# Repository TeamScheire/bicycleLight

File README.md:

# Team Scheire BicycleLight voor Carmen

Deze repository bevat de code en hardware schemas van twee deelprojecten:

1. CME (Het fietslicht en alle aanpassingen voor Carmen haar fiets)
2. SmartLight (het slimme fietslicht waarmee je een positive of negatieve fietservaring kan meedelen)

## 1. CME

In [deze folder](CME) staat de finale versie die een arduino mini gebruikt (v1.0). Zowel hardware schemas en software kan je er terug vinden.

## 2. SmartLight

In [deze folder](SmartLight) kan je volgende terug vinden:

- Hardware schema of het device en de 'bill of materials'
- Het ontwerp van de behuizing
- De firmware van het toestel
- De code voor de smartphone app (zowel android als iphone) dat de BLE (Bluetooth Low Energy) data van het toestel doorstuurt naar de backend.

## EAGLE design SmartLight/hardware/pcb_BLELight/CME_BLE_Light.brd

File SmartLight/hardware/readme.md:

# PCB

Naast de PCB en de compententen (lijst via [BOM3.xlsx](pcb_BLELight/BOM3.xlsx)) zijn er nog enkel componenten nodig die verbonden worden met de PCB en ingebouwd in de behuizing.

## Extra componenten:

### Farnell

- 1 x 1086610 -	ISR3SAD200 -  Pushbutton Switch, Off-(On), SPST-NO, 32 V, 48 V, 400 mA, Solder	4,96 euro
- 1 x 1086616 -	ISR3SAD900 -  Pushbutton Switch, Off-(On), SPST, 125 V, 50 V, 400 mA, Solder	5,80 euro
- 1 x 1638335 -	MCPAS6B2M1CE6 -  Pushbutton Switch, Off-(On), SPST, 125 V, 50 V, 400 mA, Solder	3,46 euro
- 1x 2476052 -	690-W05-260-044 -  USB Connector, Mini USB Type B, USB 1.0, Receptacle, 5 Ways, Panel Mount	5,12 euro
- 1 x 1908444 -	726141005 -  Dust Cap / Cover, Black, Dust Cap, Mini USB Type AB and Type B Connectors		0,502 euro

### Batterij
Deze lipo batterij is gebruikt: [LIPO4400mAh](https://www.olimex.com/Products/Power/BATTERY-LIPO4400mAh/)

### Rest

 - 4 x 001-M3 Multisert Messing (e.g per 1000 piece from Beluma) - these are inserts for the M3 screws
 - 4 x M3 screws
 - [Bevestiging voor het fietsstuur](https://www.dx.com/p/GACIRON-Universal-Bicycle-Handlebar-Mount-Mountain-Bike-Phone-Holder-Bike-Accessories-for-Smart-Phones-black-916491959)

## Alternatief
Het is ook perfect mogelijk om andere componenten te gebruiken (bijvoorbeeld de ESP-WROOM-32) die via UART over BLE met de app te communiceren.

Kijk bv in het stuk van de app naar [arduino code voor de esp-wroom-32](https://github.com/TeamScheire/bicycleLight/tree/master/SmartLight/app/ESP_simulation).

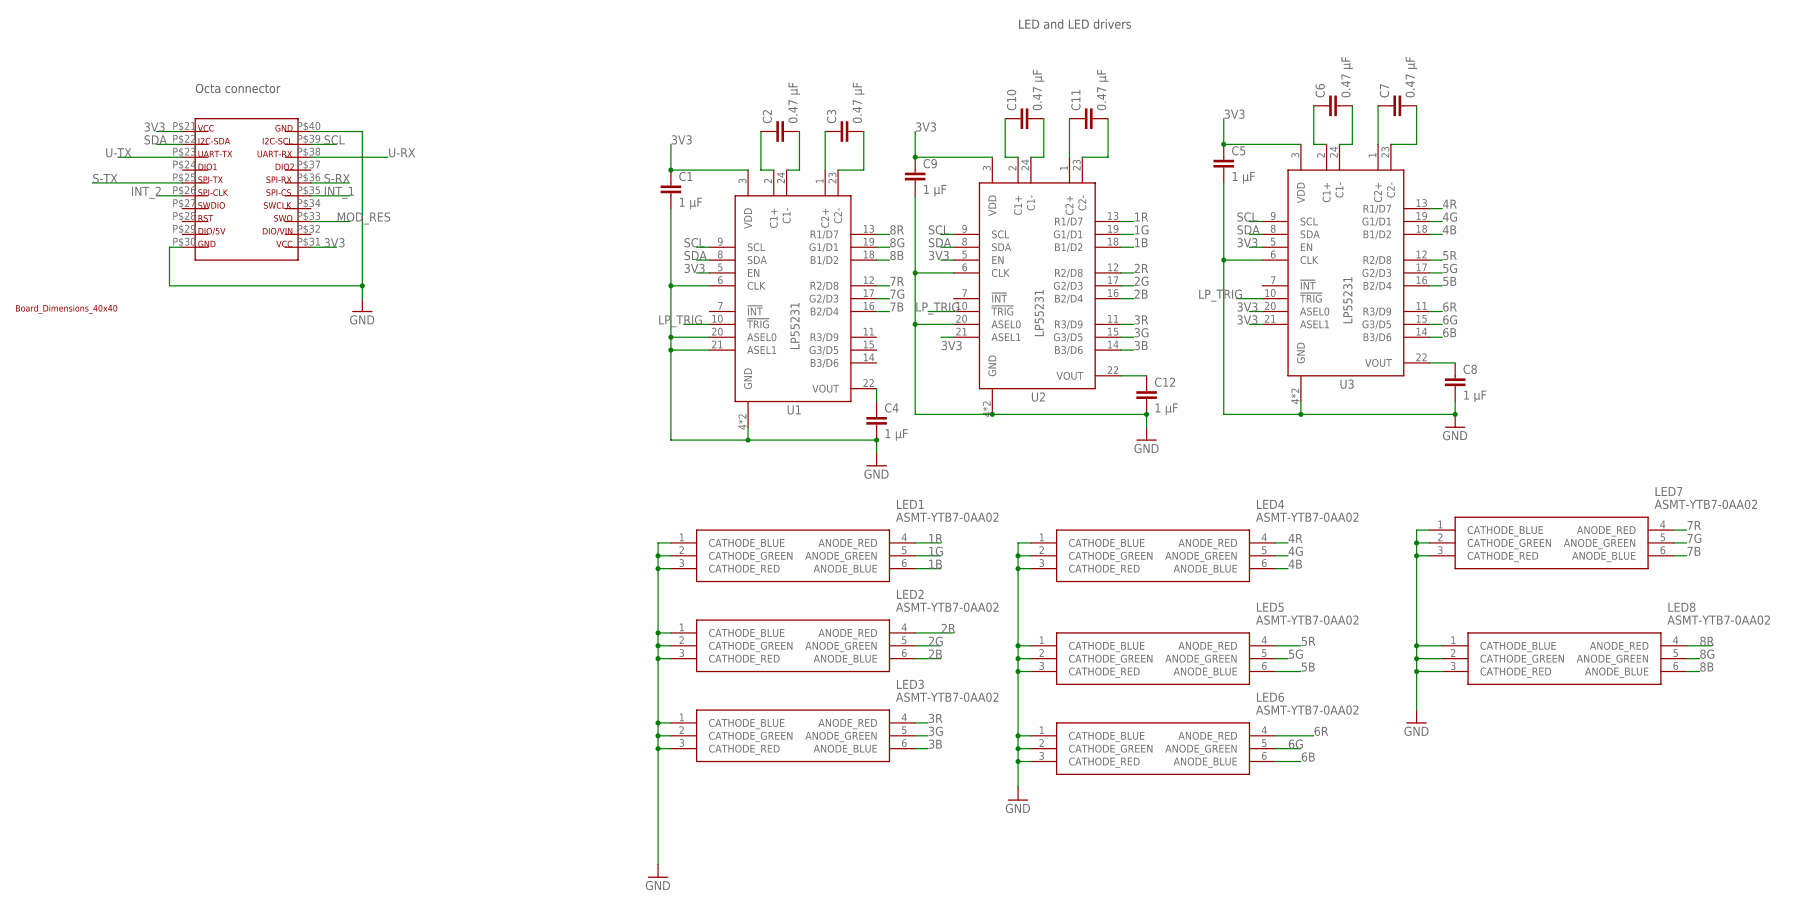
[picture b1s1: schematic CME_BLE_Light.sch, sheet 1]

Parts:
C1, C4, C5, C8, C9, C12: 1 µF; SPARKFUN_0402-CAP
C2, C3, C6, C7, C10, C11: 0.47 µF; SPARKFUN_0402-CAP
LED1, LED2, LED3, LED4, LED5, LED6, LED7, LED8: ASMT-YTB7-0AA02; ASMT-YTC7-0AA02
U1, U2, U3: LP55231; WQFN-24
U$2: OCTA-CORE_BOARD-DIMENSIONS-40X40

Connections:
1B: LED1.6 (ANODE_BLUE), U2.18 (B1/D2)
1G: LED1.5 (ANODE_GREEN), U2.19 (G1/D1)
1R: LED1.4 (ANODE_RED), U2.13 (R1/D7)
2B: LED2.6 (ANODE_BLUE), U2.16 (B2/D4)
2G: LED2.5 (ANODE_GREEN), U2.17 (G2/D3)
2R: LED2.4 (ANODE_RED), U2.12 (R2/D8)
3B: LED3.6 (ANODE_BLUE), U2.14 (B3/D6)
3G: LED3.5 (ANODE_GREEN), U2.15 (G3/D5)
3R: LED3.4 (ANODE_RED), U2.11 (R3/D9)
3V3: C1.1, C5.1, C9.1, U1.3 (VDD), U1.5 (EN), U2.3 (VDD), U2.5 (EN), U2.21 (ASEL1), U3.3 (VDD), U3.5 (EN), U3.20 (ASEL0), U3.21 (ASEL1), U$2.P$21, U$2.P$31; also elsewhere on the board
4B: LED4.6 (ANODE_BLUE), U3.18 (B1/D2)
4G: LED4.5 (ANODE_GREEN), U3.19 (G1/D1)
4R: LED4.4 (ANODE_RED), U3.13 (R1/D7)
5B: LED5.6 (ANODE_BLUE), U3.16 (B2/D4)
5G: LED5.5 (ANODE_GREEN), U3.17 (G2/D3)
5R: LED5.4 (ANODE_RED), U3.12 (R2/D8)
6B: LED6.6 (ANODE_BLUE), U3.14 (B3/D6)
6G: LED6.5 (ANODE_GREEN), U3.15 (G3/D5)
6R: LED6.4 (ANODE_RED), U3.11 (R3/D9)
7B: LED7.6 (ANODE_BLUE), U1.16 (B2/D4)
7G: LED7.5 (ANODE_GREEN), U1.17 (G2/D3)
7R: LED7.4 (ANODE_RED), U1.12 (R2/D8)
8B: LED8.6 (ANODE_BLUE), U1.18 (B1/D2)
8G: LED8.5 (ANODE_GREEN), U1.19 (G1/D1)
8R: LED8.4 (ANODE_RED), U1.13 (R1/D7)
GND: C1.2, C4.2, C5.2, C8.2, C9.2, C12.2, LED1.1 (CATHODE_BLUE), LED1.2 (CATHODE_GREEN), LED1.3 (CATHODE_RED), LED2.1 (CATHODE_BLUE), LED2.2 (CATHODE_GREEN), LED2.3 (CATHODE_RED), LED3.1 (CATHODE_BLUE), LED3.2 (CATHODE_GREEN), LED3.3 (CATHODE_RED), LED4.1 (CATHODE_BLUE), LED4.2 (CATHODE_GREEN), LED4.3 (CATHODE_RED), LED5.1 (CATHODE_BLUE), LED5.2 (CATHODE_GREEN), LED5.3 (CATHODE_RED), LED6.1 (CATHODE_BLUE), LED6.2 (CATHODE_GREEN), LED6.3 (CATHODE_RED), LED7.1 (CATHODE_BLUE), LED7.2 (CATHODE_GREEN), LED7.3 (CATHODE_RED), LED8.1 (CATHODE_BLUE), LED8.2 (CATHODE_GREEN), LED8.3 (CATHODE_RED), U1.4 (GND), U1.6 (CLK), U1.20 (ASEL0), U1.21 (ASEL1), U1.EP (GND), U2.4 (GND), U2.6 (CLK), U2.20 (ASEL0), U2.EP (GND), U3.4 (GND), U3.6 (CLK), U3.EP (GND), U$2.P$30, U$2.P$40; also elsewhere on the board
INT_1: U$2.P$35; also elsewhere on the board
INT_2: U$2.P$26; also elsewhere on the board
LP_TRIG: U1.10 (!TRIG), U2.10 (!TRIG), U3.10 (!TRIG); also elsewhere on the board
MOD_RES: U$2.P$33; also elsewhere on the board
unnamed: C2.2, U1.24 (C1-)
unnamed: C2.1, U1.2 (C1+)
unnamed: C3.1, U1.1 (C2+)
unnamed: C3.2, U1.23 (C2-)
unnamed: C10.1, U2.2 (C1+)
unnamed: C10.2, U2.24 (C1-)
unnamed: C11.1, U2.1 (C2+)
unnamed: C11.2, U2.23 (C2-)
unnamed: C6.1, U3.2 (C1+)
unnamed: C6.2, U3.24 (C1-)
unnamed: C7.1, U3.1 (C2+)
unnamed: C7.2, U3.23 (C2-)
unnamed: C4.1, U1.22 (VOUT)
unnamed: C12.1, U2.22 (VOUT)
unnamed: C8.1, U3.22 (VOUT)
S-RX: U$2.P$36; also elsewhere on the board
S-TX: U$2.P$25; also elsewhere on the board
SCL: U1.9 (SCL), U2.9 (SCL), U3.9 (SCL), U$2.P$39; also elsewhere on the board
SDA: U1.8 (SDA), U2.8 (SDA), U3.8 (SDA), U$2.P$22; also elsewhere on the board
U-RX: U$2.P$38; also elsewhere on the board
U-TX: U$2.P$23; also elsewhere on the board

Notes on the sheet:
Octa connector
LED and LED drivers

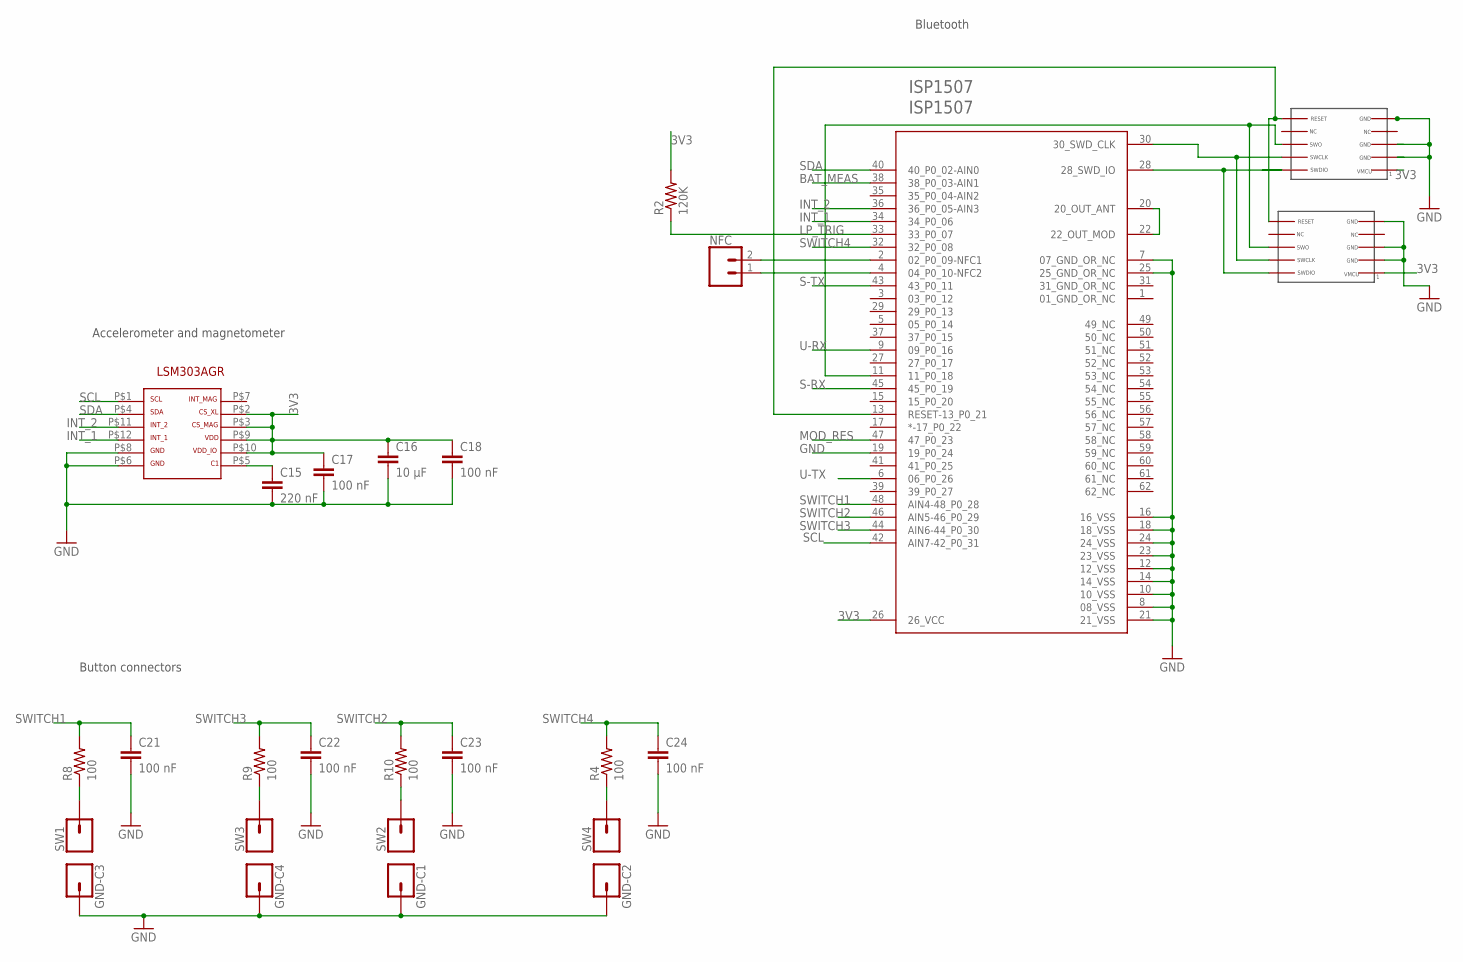
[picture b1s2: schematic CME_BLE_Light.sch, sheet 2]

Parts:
C15: 220 nF; SPARKFUN_0402-CAP
C16: 10 µF; SPARKFUN_0402-CAP
C17, C18, C21, C22, C23, C24: 100 nF; SPARKFUN_0402-CAP
GND-C1, GND-C2, GND-C3, GND-C4: CONN_01; 1X01
ISP1507: ISP1507
LSM303AGR: LSM303AGRTR
NFC: CONN_02; 1X02
R2: 120K; SPARKFUN_0402-RES
R4, R8, R9, R10: 100; SPARKFUN_0402-RES
SW1, SW2, SW3, SW4: CONN_01; 1X01
U$1, U$3: DRAGAN-PERSONAL_SEGGER-CONN

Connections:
01_GND_OR_NC: ISP1507.1 (01_GND_OR_NC)
3V3: C16.1, C17.1, C18.1, ISP1507.26 (26_VCC), LSM303AGR.P$2, LSM303AGR.P$3, LSM303AGR.P$9, LSM303AGR.P$10, R2.2, U$1.P$5, U$3.P$5; also elsewhere on the board
31_GND_OR_NC: ISP1507.31 (31_GND_OR_NC)
BAT_MEAS: ISP1507.38 (38_P0_03-AIN1); also elsewhere on the board
GND: C15.2, C16.2, C17.2, C18.2, C21.2, C22.2, C23.2, C24.2, GND-C1.1, GND-C2.1, GND-C3.1, GND-C4.1, ISP1507.7 (07_GND_OR_NC), ISP1507.8 (08_VSS), ISP1507.10 (10_VSS), ISP1507.12 (12_VSS), ISP1507.14 (14_VSS), ISP1507.16 (16_VSS), ISP1507.18 (18_VSS), ISP1507.19 (19_P0_24), ISP1507.21 (21_VSS), ISP1507.23 (23_VSS), ISP1507.24 (24_VSS), ISP1507.25 (25_GND_OR_NC), LSM303AGR.P$6, LSM303AGR.P$8, U$1.P$1, U$1.P$3, U$1.P$4, U$3.P$1, U$3.P$3, U$3.P$4; also elsewhere on the board
INT_1: ISP1507.34 (34_P0_06), LSM303AGR.P$12; also elsewhere on the board
INT_2: ISP1507.36 (36_P0_05-AIN3), LSM303AGR.P$11; also elsewhere on the board
LP_TRIG: ISP1507.33 (33_P0_07), R2.1; also elsewhere on the board
MOD_RES: ISP1507.47 (47_P0_23); also elsewhere on the board
unnamed: C15.1, LSM303AGR.P$5
unnamed: ISP1507.20 (20_OUT_ANT), ISP1507.22 (22_OUT_MOD)
unnamed: ISP1507.2 (02_P0_09-NFC1), NFC.2
unnamed: ISP1507.4 (04_P0_10-NFC2), NFC.1
unnamed: R8.1, SW1.1
unnamed: R10.1, SW2.1
unnamed: R9.1, SW3.1
unnamed: R4.1, SW4.1
RST: ISP1507.13 (RESET-13_P0_21), U$1.P$10, U$3.P$10
S-RX: ISP1507.45 (45_P0_19); also elsewhere on the board
S-TX: ISP1507.43 (43_P0_11); also elsewhere on the board
SCL: ISP1507.42 (AIN7-42_P0_31), LSM303AGR.P$1; also elsewhere on the board
SDA: ISP1507.40 (40_P0_02-AIN0), LSM303AGR.P$4; also elsewhere on the board
SWCLK: ISP1507.30 (30_SWD_CLK), U$1.P$7, U$3.P$7
SWDIO: ISP1507.28 (28_SWD_IO), U$1.P$6, U$3.P$6
SWITCH1: C21.1, ISP1507.48 (AIN4-48_P0_28), R8.2
SWITCH2: C23.1, ISP1507.46 (AIN5-46_P0_29), R10.2
SWITCH3: C22.1, ISP1507.44 (AIN6-44_P0_30), R9.2
SWITCH4: C24.1, ISP1507.32 (32_P0_08), R4.2
SWO: ISP1507.11 (11_P0_18), U$1.P$8, U$3.P$8
U-RX: ISP1507.9 (09_P0_16); also elsewhere on the board
U-TX: ISP1507.6 (06_P0_26); also elsewhere on the board

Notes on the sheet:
Bluetooth
Accelerometer and magnetometer
Button connectors

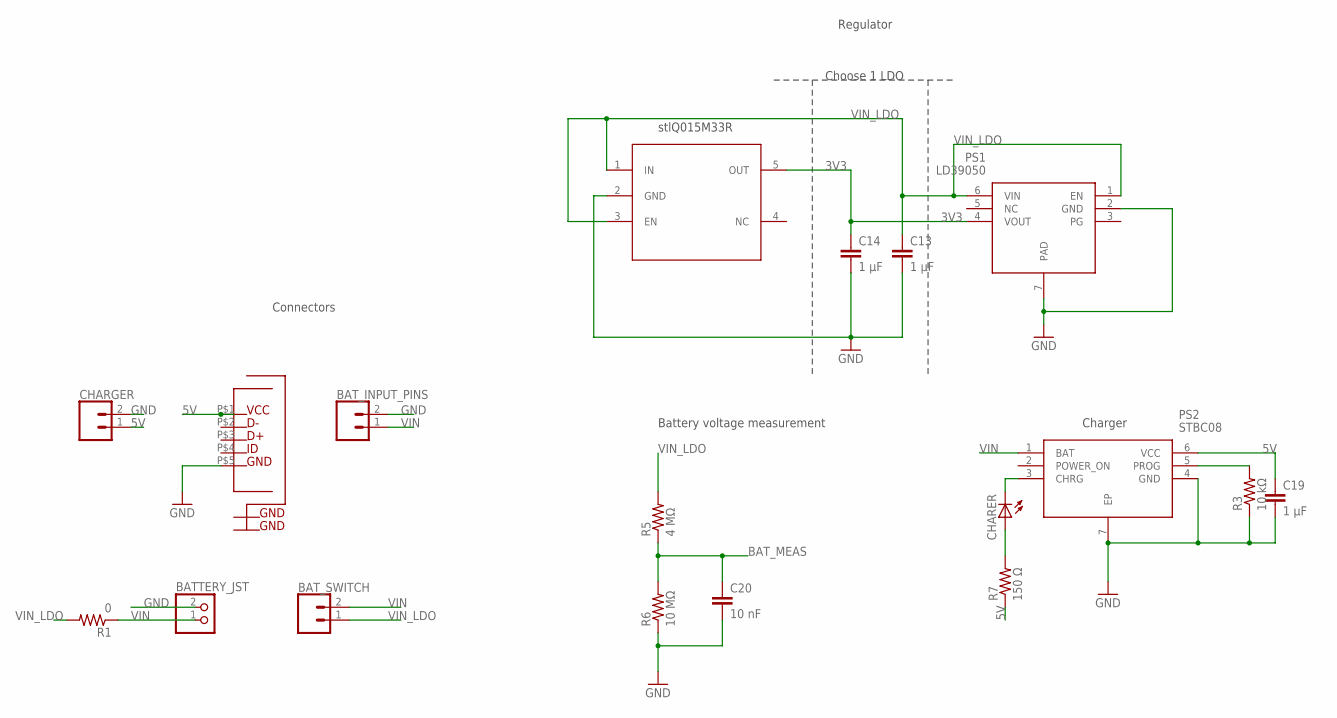
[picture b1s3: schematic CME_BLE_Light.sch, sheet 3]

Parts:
BATTERY_JST: ADAFRUIT_JST_2PIN-SMT-RA; ADAFRUIT_JST-PH-2-SMT-RA
BAT_INPUT_PINS: CONN_02; 1X02
BAT_SWITCH: CONN_02; 1X02
C13, C14, C19: 1 µF; SPARKFUN_0402-CAP
C20: 10 nF; SPARKFUN_0402-CAP
CHARER: LED_LEDSML0603; LED_SML0603
CHARGER: CONN_02; 1X02
PS1: LD39050; SON95P300X300X100-7N
PS2: STBC08; SON95P300X300X100-7N
R1: 0; SPARKFUN_0402-RES
R3: 10 kΩ; SPARKFUN_0402-RES
R5: 4 MΩ; SPARKFUN_0402-RES
R6: 10 MΩ; SPARKFUN_0402-RES
R7: 150 Ω; SPARKFUN_0402-RES
STLQ015: STLQ015M33R; SOT95P290X145-5N
U$4: OCTA-CORE_MCIRO-USB2; OCTA-CORE_MICRO-USB2

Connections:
3V3: C14.1, PS1.4 (VOUT), STLQ015.5 (OUT); also elsewhere on the board
5V: C19.1, CHARGER.1, PS2.6 (VCC), R7.1, U$4.P$1
BAT_MEAS: C20.1, R5.1, R6.2; also elsewhere on the board
GND: BATTERY_JST.2 (1), BAT_INPUT_PINS.2, C13.2, C14.2, C19.2, C20.2, CHARGER.2, PS1.2 (GND), PS1.7 (PAD), PS2.4 (GND), PS2.7 (EP), R3.1, R6.1, STLQ015.2 (GND), U$4.P$5; also elsewhere on the board
unnamed: PS2.5 (PROG), R3.2
unnamed: CHARER.C, PS2.3 (CHRG)
unnamed: CHARER.A, R7.2
VIN: BATTERY_JST.1 (2), BAT_INPUT_PINS.1, BAT_SWITCH.2, PS2.1 (BAT), R1.1
VIN_LDO: BAT_SWITCH.1, C13.1, PS1.1 (EN), PS1.6 (VIN), R1.2, R5.2, STLQ015.1 (IN), STLQ015.3 (EN)

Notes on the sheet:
stlQ015M33R
Choose 1 LDO
Charger
Battery voltage measurement
Regulator
Connectors

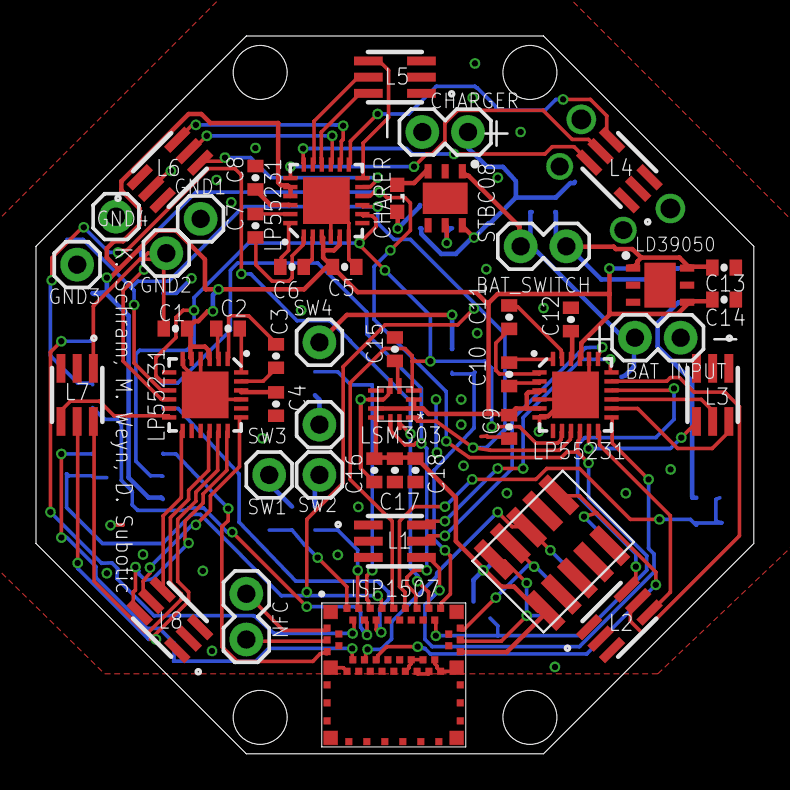
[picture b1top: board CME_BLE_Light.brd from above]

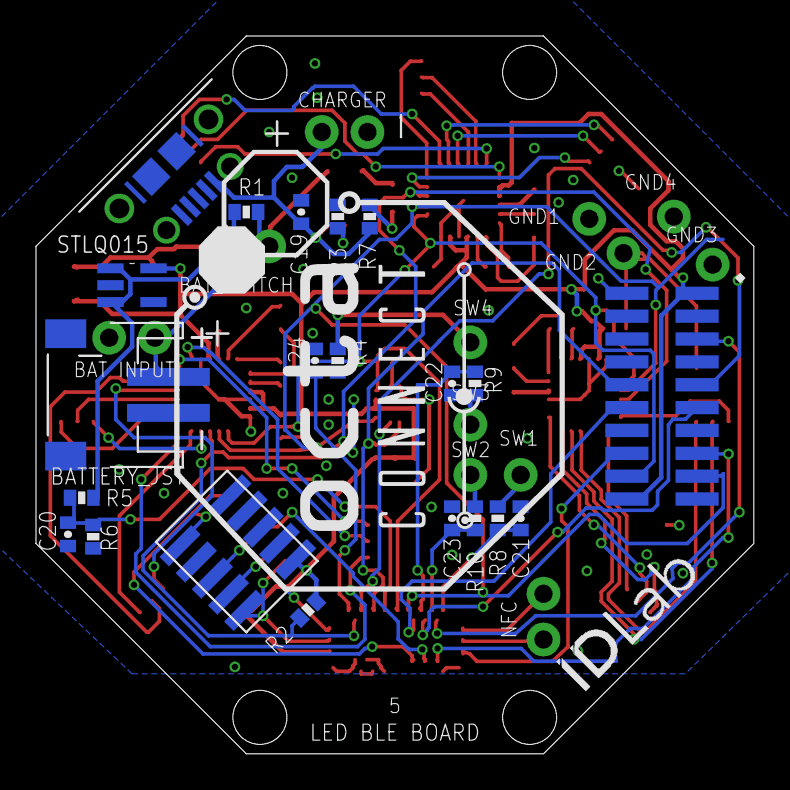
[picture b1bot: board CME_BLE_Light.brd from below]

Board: 2 copper layers, 39.9 x 39.9 mm, 68 parts (20 on the bottom side), 74 nets.

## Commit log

2018-08-30 added ios plist config strings to config.xml
2018-08-30 first working version: ble-mqtt-gps
2018-08-30 test ino for esp32 ble shield (esp-wroom-32)
2018-08-30 refactoring
2018-08-30 bugfixes all over the place first build for ios
2018-08-30 better background location implementation (i hope)
2018-08-30 additional ios settings
2018-08-30 mqtt messages are cached on disconnection
2018-08-30 background gps fix (to test) username is sent in stead of hardcoded usertoken
2018-08-30 fine tuning app permissions for ios
2018-08-30 bugfix ui device page
2018-08-30 added for testflight submission
2018-08-30 mqtt connection and basic data structure navigation in app basic home screen
2018-08-30 user scaffolding
2018-08-30 initial commit with skeleton for the app
2018-08-30 small tweaks
2018-08-30 cleanup
2018-08-30 bugfix
2018-08-30 bugfix in protocol
2018-08-30 no blf prefix in entityId
2018-08-30 - trying to reconnect with ble on app activation - small cleanup in background location methods
2018-08-30 ua settings
2018-08-30 mqtt.js testen
2018-08-30 new mqtt settings
2018-08-30 new mqtt library
2018-08-30 adding ios build
2018-08-30 optimising build for ios
2018-08-30 ios icons
2018-08-30 new location services plugin to make background tracking possible on iOS
2018-09-03 added ble back to package.json
2018-09-07 cleanup logo's
2018-09-07 added android to config
2018-09-08 removed gps debug info for users
2018-09-11 no spaces in username
2018-09-11 fix for spaces in username
2018-09-19 moved files to app to prepare other data of the fix
2018-09-19 removed other files
2018-09-19 moved npmignore
2018-11-03 Moved app to SmartLight
2018-11-03 initial description of repo
2018-11-03 creating map structure
2018-11-03 Arduino code for CME
2018-11-03 translated readme to dutch
2018-11-03 enclosure
2018-11-03 enclosure screenshot
2018-11-03 files used for production
2018-11-03 arduino code of final setup including horn
2018-11-03 copy of firmware code
2018-11-03 adapt code to sdk v15.2
2018-11-03 additional components for enclosure
2018-11-03 renamed readme
2018-11-03 added eagle submodule
2018-11-03 put CME schematic in draft eagle
2018-11-03 updated schematic
2018-11-03 adapt gitmodules to ingore dirty eagle arduino (ignore changes)
2018-11-03 fixed on of the many typos
2018-11-12 license added
2018-11-12 ignore platforms
2018-11-15 added inline doc
2018-11-15 readme for Smartlight app
2018-11-15 smartligh app readme
2018-11-15 geen app/platforms meer
2018-11-15 text-corrections
2018-11-18 updating links
2018-11-18 adding readme files
2018-11-18 reoganizing files
2018-11-18 updating readme
2018-11-19 corrections
2018-11-19 extra screenshots
2018-11-19 textcorrections
2018-11-19 text-corrections, cleanup
2018-11-21 module updates
2018-11-21 cleanup platforms
2018-12-03 icons and screens added

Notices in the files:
parts and their libraries:
SparkFun-Connectors: Licensing: Creative Commons ShareAlike 4.0 International - https://creativecommons.org/licenses/by-sa/4.0
